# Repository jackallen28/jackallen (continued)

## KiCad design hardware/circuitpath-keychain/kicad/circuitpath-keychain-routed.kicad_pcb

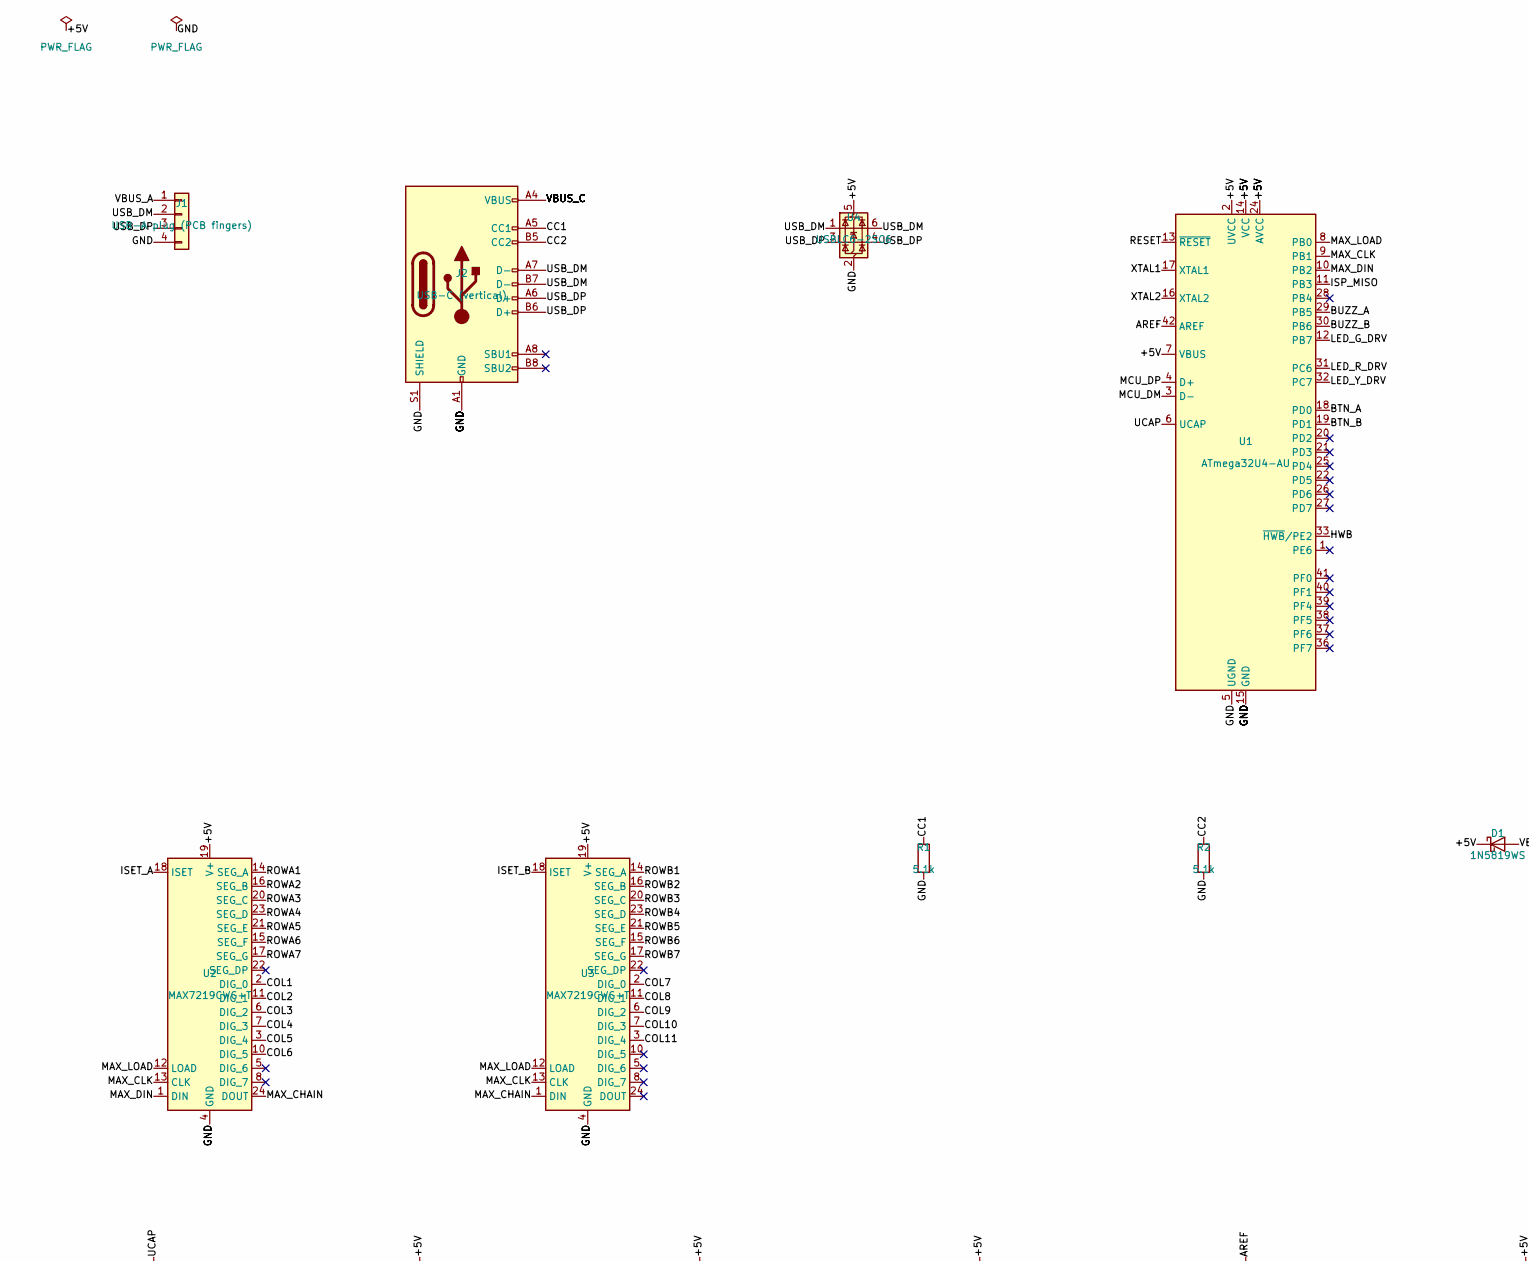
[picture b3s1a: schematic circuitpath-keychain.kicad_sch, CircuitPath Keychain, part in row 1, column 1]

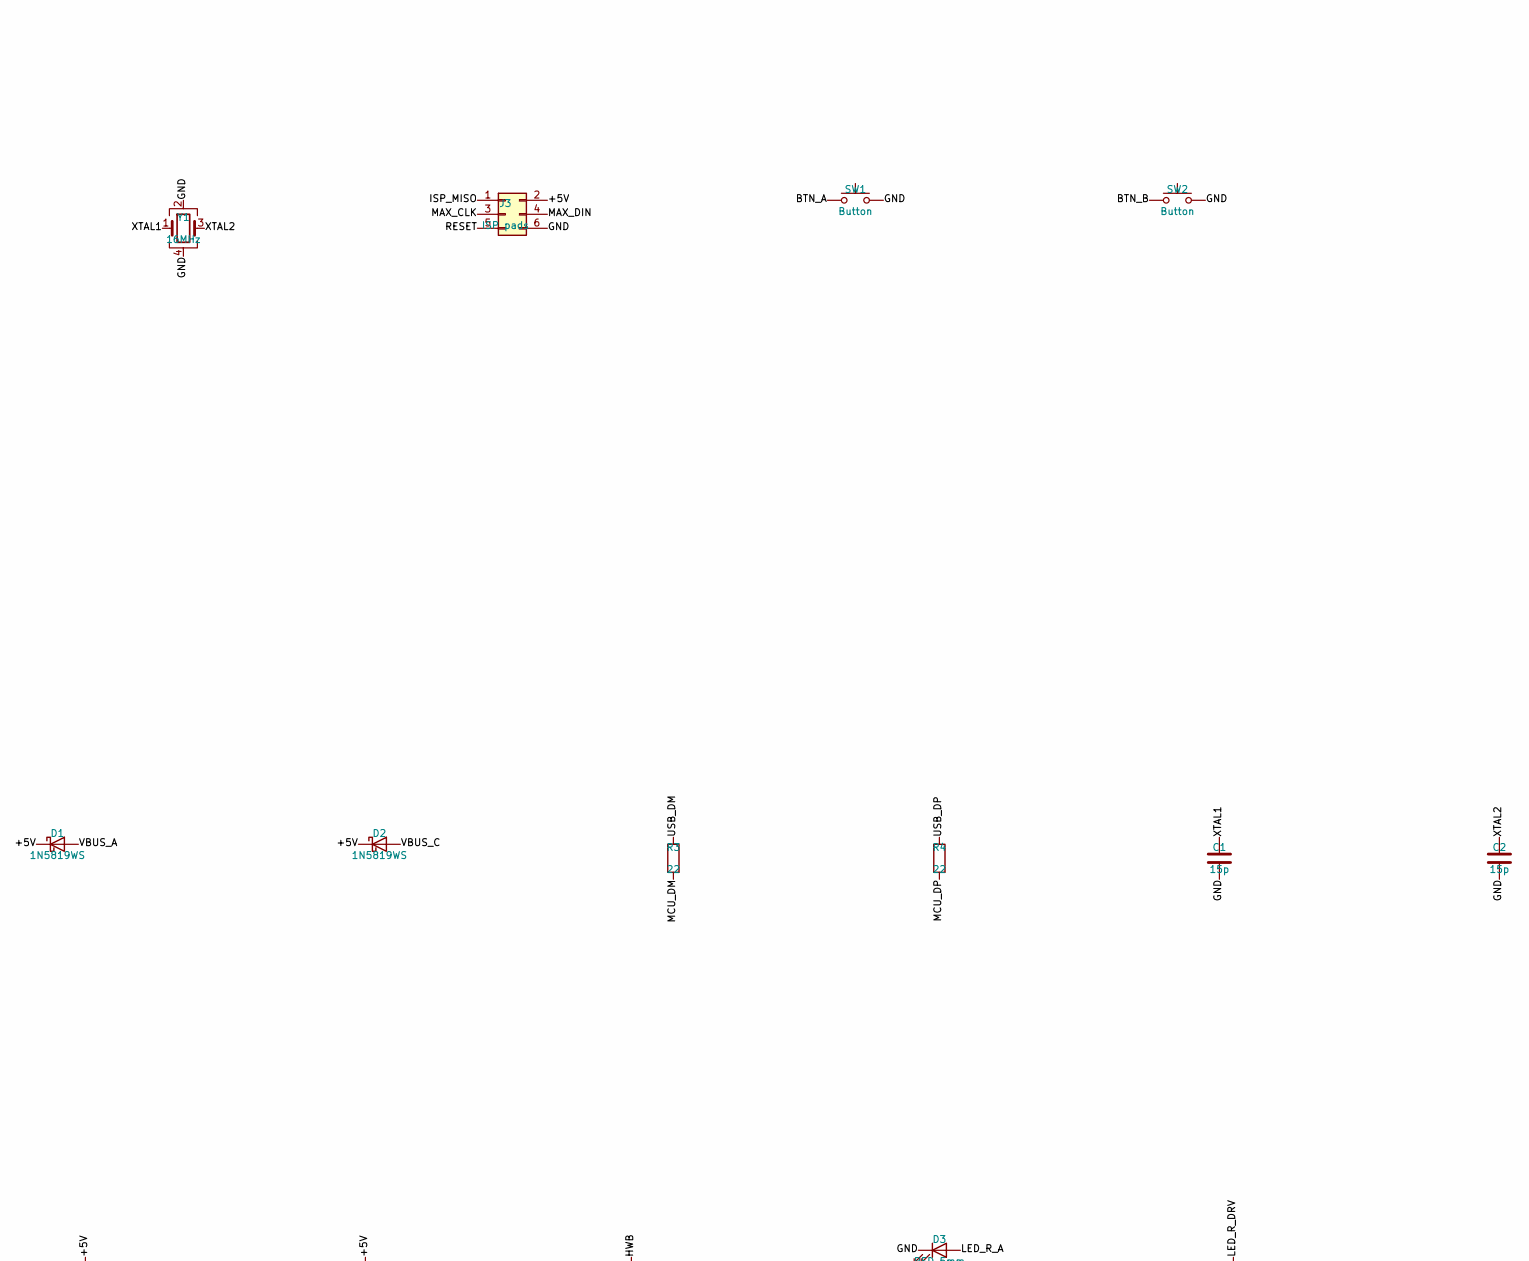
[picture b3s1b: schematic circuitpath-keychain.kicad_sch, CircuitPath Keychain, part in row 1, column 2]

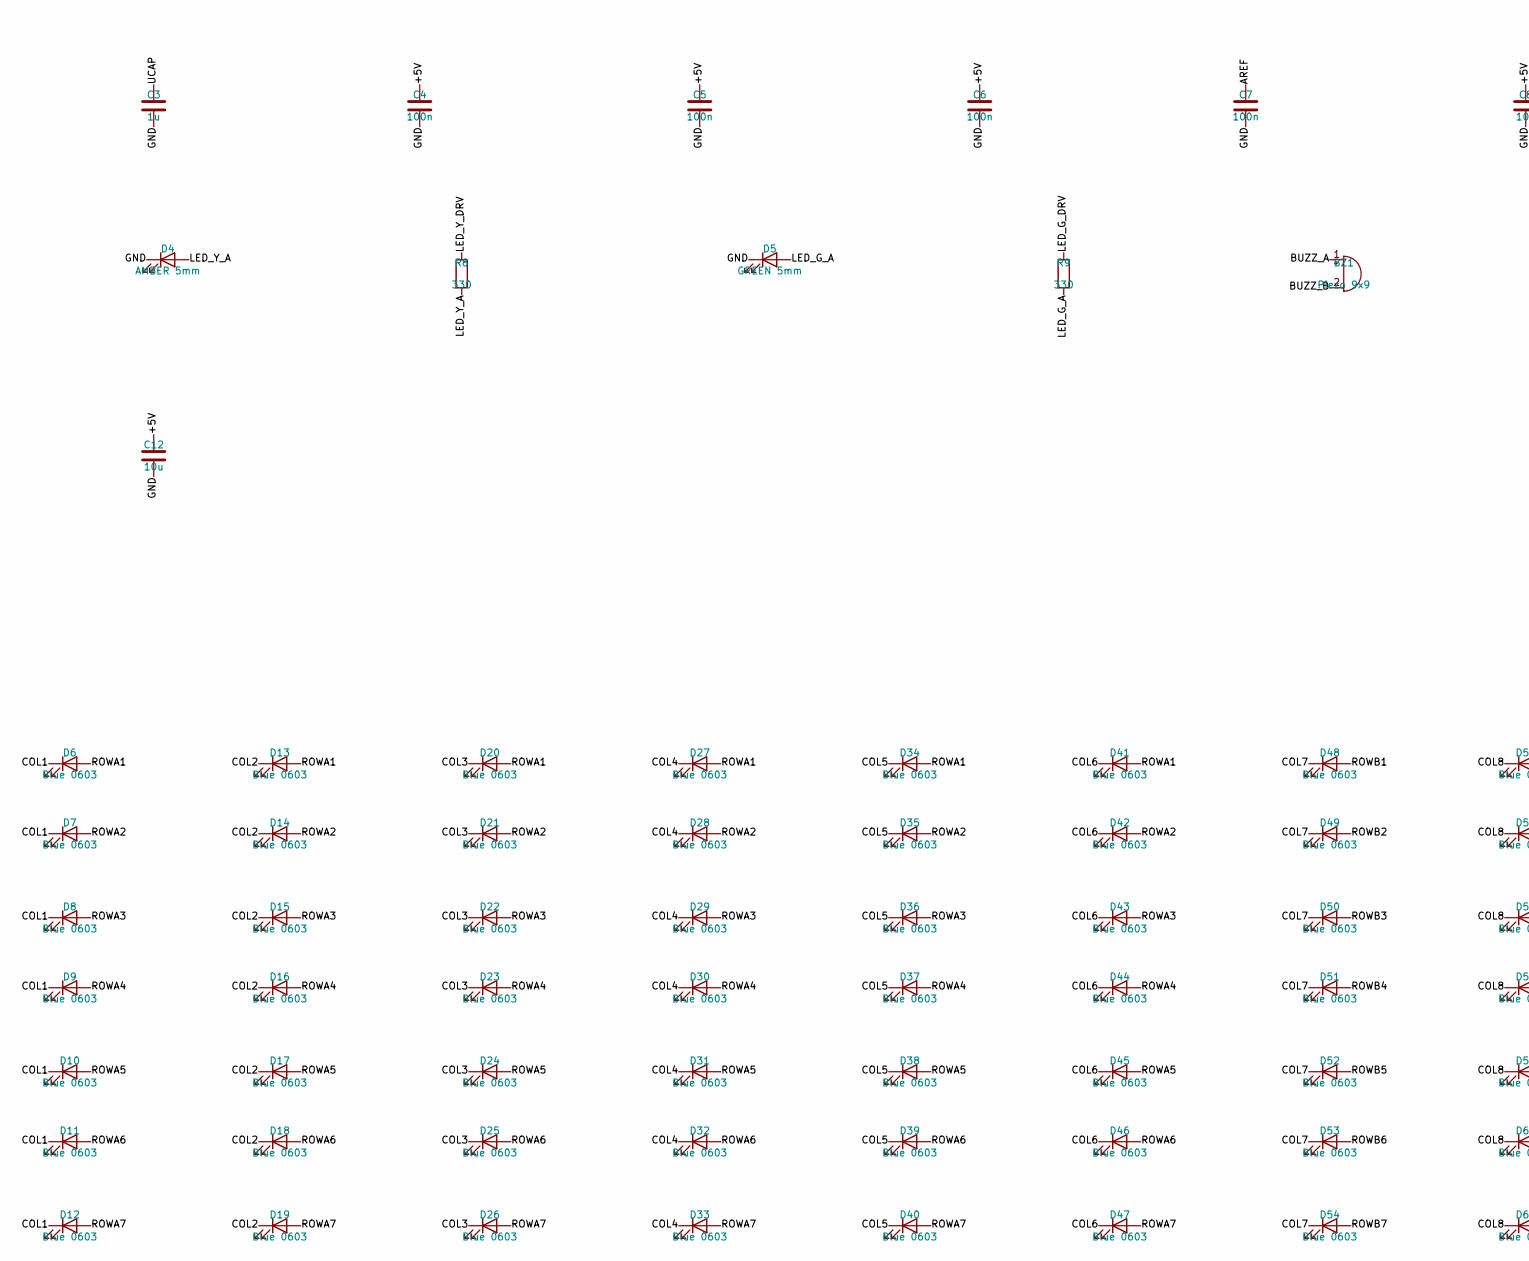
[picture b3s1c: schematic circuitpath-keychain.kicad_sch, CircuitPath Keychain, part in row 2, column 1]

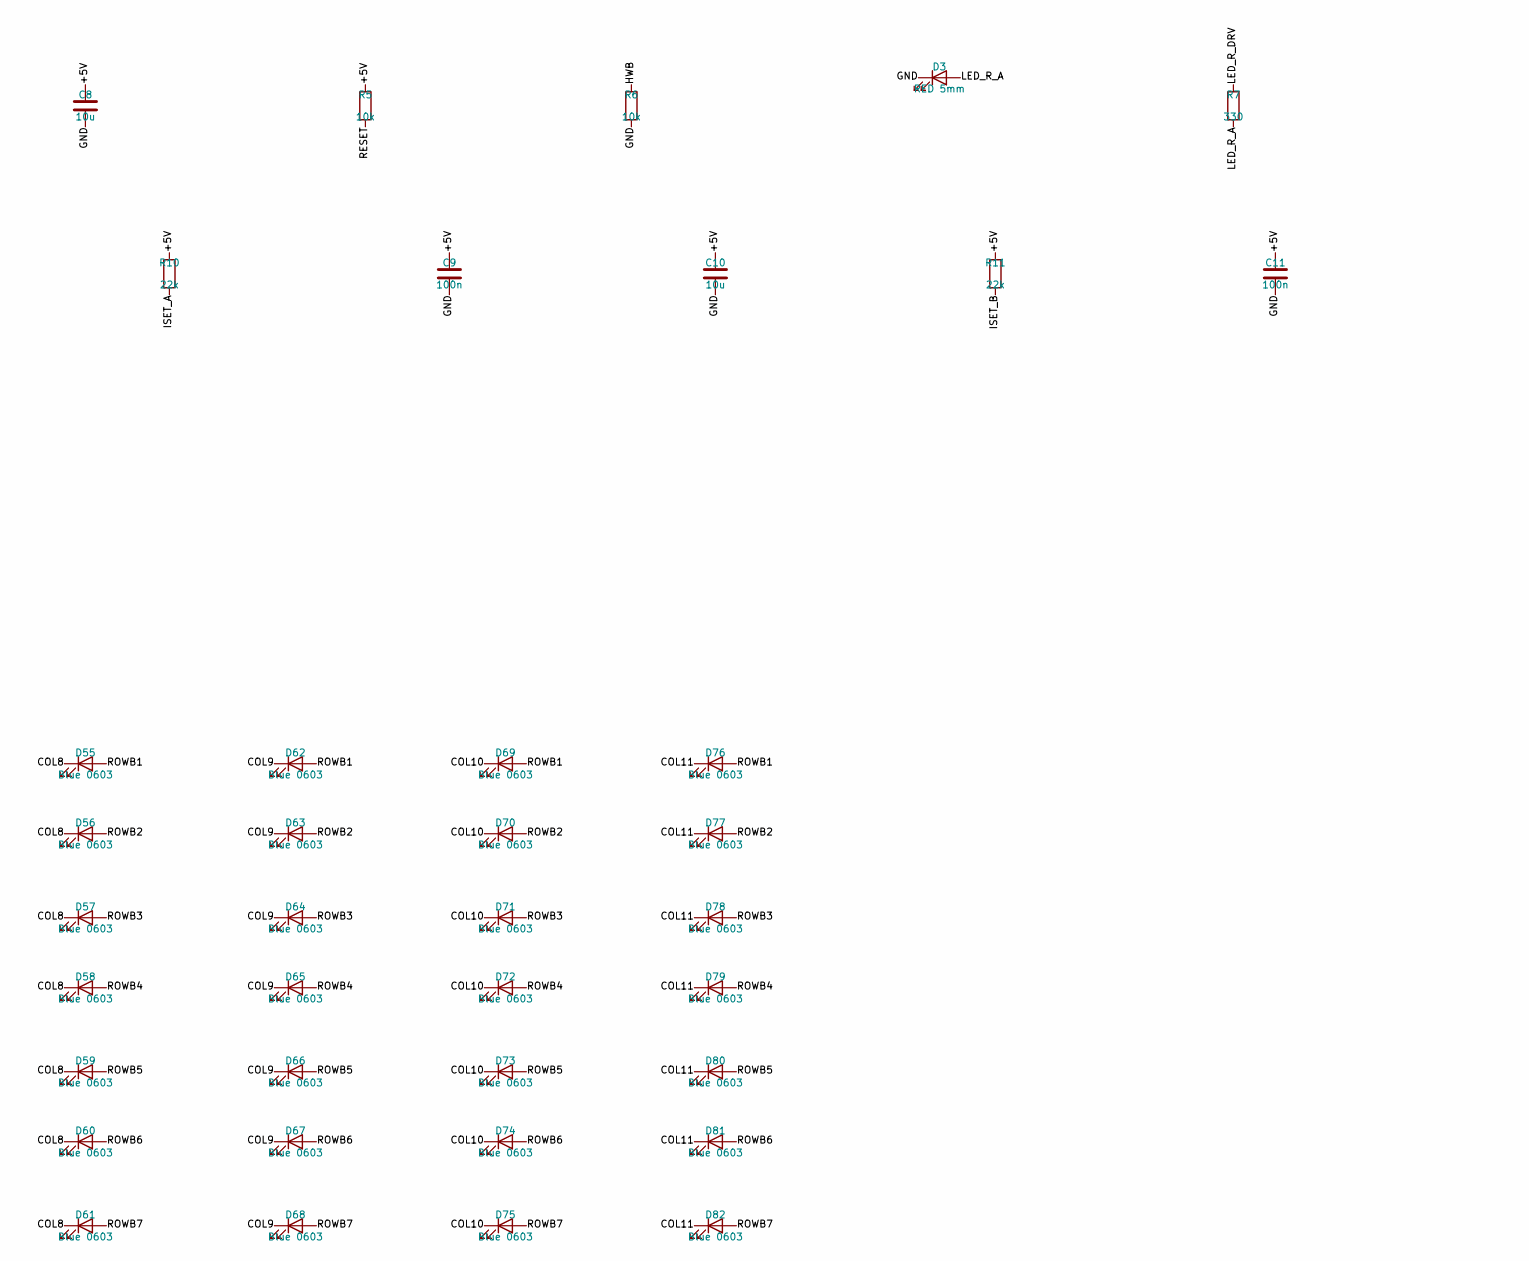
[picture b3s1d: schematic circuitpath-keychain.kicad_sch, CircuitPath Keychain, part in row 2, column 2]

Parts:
BZ1: Piezo 9x9; Buzzer_Murata_PKMCS0909E; MPN PKMCS0909E4000-R1; LCSC C910763
C1, C2: 15p; C_0603_1608Metric; MPN CL10C150JB8NNNC; LCSC C1644
C3: 1u; C_0603_1608Metric; MPN CL10A105KB8NNNC; LCSC C15849
C4, C5, C6, C7, C9, C11: 100n; C_0603_1608Metric; MPN CL10B104KB8NNNC; LCSC C14663
C8, C10, C12: 10u; C_0805_2012Metric; MPN CL21A106KAYNNNE; LCSC C15850
D1, D2: 1N5819WS; D_SOD-323; MPN 1N5819WS; LCSC C191023
D3: RED 5mm; LED_D5.0mm
D4: AMBER 5mm; LED_D5.0mm
D5: GREEN 5mm; LED_D5.0mm
D6, D7, D8, D9, D10, D11, D12, D13, D14, D15, D16, D17, D18, D19, D20, D21, D22, D23, D24, D25, D26, D27, D28, D29, D30, D31, D32, D33, D34, D35, D36, D37, D38, D39, D40, D41, D42, D43, D44, D45, D46, D47, D48, D49, D50, D51, D52, D53, D54, D55, D56, D57, D58, D59, D60, D61, D62, D63, D64, D65, D66, D67, D68, D69, D70, D71, D72, D73, D74, D75, D76, D77, D78, D79, D80, D81, D82: Blue 0603; LED_0603_1608Metric; MPN KT-0603B; LCSC C2288
J1: USB-A plug (PCB fingers); USB_A_PCB_Plug
J2: USB-C (vertical); USB_C_Receptacle_G-Switch_GT-USB-7051x; MPN GT-USB-7051A; LCSC C2843970
J3: ISP pads; ISP_Pads_2x3
R1, R2: 5.1k; R_0603_1608Metric; MPN 0603WAF5101T5E; LCSC C23186
R3, R4: 22; R_0603_1608Metric; MPN 0603WAF220JT5E; LCSC C23345
R5, R6: 10k; R_0603_1608Metric; MPN 0603WAF1002T5E; LCSC C25804
R7, R8, R9: 330; R_0603_1608Metric; MPN 0603WAF3300T5E; LCSC C23138
R10, R11: 22k; R_0603_1608Metric; MPN 0603WAF2202T5E; LCSC C31850
SW1, SW2: Button; SW_Push_1P1T_XKB_TS-1187A; MPN TS-1187A-B-A-B; LCSC C318884
U1: ATmega32U4-AU; TQFP-44_10x10mm_P0.8mm; MPN ATMEGA32U4-AU; LCSC C44854
U2, U3: MAX7219CWG+T; SOIC-24W_7.5x15.4mm_P1.27mm; MPN MAX7219CWG+T; LCSC C9964
U4: USBLC6-2SC6; SOT-23-6; MPN USBLC6-2SC6; LCSC C7519
Y1: 16MHz; Crystal_SMD_3225-4Pin_3.2x2.5mm; MPN X322516MLB4SI; LCSC C13738

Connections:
+5V: C4.1, C5.1, C6.1, C8.1, C9.1, C10.1, C11.1, C12.1, D1.1 (K), D2.1 (K), J3.2, R5.1, R10.1, R11.1, U1.2 (UVCC), U1.7 (VBUS), U1.14 (VCC), U1.24 (AVCC), U1.34 (VCC), U1.44 (AVCC), U2.19 (V+), U3.19 (V+), U4.5 (VBUS)
AREF: C7.1, U1.42 (AREF)
BTN_A: SW1.1, U1.18 (PD0)
BTN_B: SW2.1, U1.19 (PD1)
BUZZ_A: BZ1.1 (+), U1.29 (PB5)
BUZZ_B: BZ1.2 (-), U1.30 (PB6)
CC1: J2.A5 (CC1), R1.1
CC2: J2.B5 (CC2), R2.1
COL1: D6.1 (K), D7.1 (K), D8.1 (K), D9.1 (K), D10.1 (K), D11.1 (K), D12.1 (K), U2.2 (DIG_0)
COL2: D13.1 (K), D14.1 (K), D15.1 (K), D16.1 (K), D17.1 (K), D18.1 (K), D19.1 (K), U2.11 (DIG_1)
COL3: D20.1 (K), D21.1 (K), D22.1 (K), D23.1 (K), D24.1 (K), D25.1 (K), D26.1 (K), U2.6 (DIG_2)
COL4: D27.1 (K), D28.1 (K), D29.1 (K), D30.1 (K), D31.1 (K), D32.1 (K), D33.1 (K), U2.7 (DIG_3)
COL5: D34.1 (K), D35.1 (K), D36.1 (K), D37.1 (K), D38.1 (K), D39.1 (K), D40.1 (K), U2.3 (DIG_4)
COL6: D41.1 (K), D42.1 (K), D43.1 (K), D44.1 (K), D45.1 (K), D46.1 (K), D47.1 (K), U2.10 (DIG_5)
COL7: D48.1 (K), D49.1 (K), D50.1 (K), D51.1 (K), D52.1 (K), D53.1 (K), D54.1 (K), U3.2 (DIG_0)
COL8: D55.1 (K), D56.1 (K), D57.1 (K), D58.1 (K), D59.1 (K), D60.1 (K), D61.1 (K), U3.11 (DIG_1)
COL9: D62.1 (K), D63.1 (K), D64.1 (K), D65.1 (K), D66.1 (K), D67.1 (K), D68.1 (K), U3.6 (DIG_2)
COL10: D69.1 (K), D70.1 (K), D71.1 (K), D72.1 (K), D73.1 (K), D74.1 (K), D75.1 (K), U3.7 (DIG_3)
COL11: D76.1 (K), D77.1 (K), D78.1 (K), D79.1 (K), D80.1 (K), D81.1 (K), D82.1 (K), U3.3 (DIG_4)
GND: C1.2, C2.2, C3.2, C4.2, C5.2, C6.2, C7.2, C8.2, C9.2, C10.2, C11.2, C12.2, D3.1 (K), D4.1 (K), D5.1 (K), J1.4, J2.A1 (GND), J2.A12 (GND), J2.B1 (GND), J2.B12 (GND), J2.S1 (SHIELD), J3.6, R1.2, R2.2, R6.2, SW1.2, SW2.2, U1.5 (UGND), U1.15 (GND), U1.23 (GND), U1.35 (GND), U1.43 (GND), U2.4 (GND), U2.9 (GND), U3.4 (GND), U3.9 (GND), U4.2 (GND), Y1.2, Y1.4
HWB: R6.1, U1.33 (~HWB/PE2)
ISET_A: R10.2, U2.18 (ISET)
ISET_B: R11.2, U3.18 (ISET)
ISP_MISO: J3.1, U1.11 (PB3)
LED_G_A: D5.2 (A), R9.2
LED_G_DRV: R9.1, U1.12 (PB7)
LED_R_A: D3.2 (A), R7.2
LED_R_DRV: R7.1, U1.31 (PC6)
LED_Y_A: D4.2 (A), R8.2
LED_Y_DRV: R8.1, U1.32 (PC7)
MAX_CHAIN: U2.24 (DOUT), U3.1 (DIN)
MAX_CLK: J3.3, U1.9 (PB1), U2.13 (CLK), U3.13 (CLK)
MAX_DIN: J3.4, U1.10 (PB2), U2.1 (DIN)
MAX_LOAD: U1.8 (PB0), U2.12 (LOAD), U3.12 (LOAD)
MCU_DM: R3.2, U1.3 (D-)
MCU_DP: R4.2, U1.4 (D+)
RESET: J3.5, R5.2, U1.13 (~RESET)
ROWA1: D6.2 (A), D13.2 (A), D20.2 (A), D27.2 (A), D34.2 (A), D41.2 (A), U2.14 (SEG_A)
ROWA2: D7.2 (A), D14.2 (A), D21.2 (A), D28.2 (A), D35.2 (A), D42.2 (A), U2.16 (SEG_B)
ROWA3: D8.2 (A), D15.2 (A), D22.2 (A), D29.2 (A), D36.2 (A), D43.2 (A), U2.20 (SEG_C)
ROWA4: D9.2 (A), D16.2 (A), D23.2 (A), D30.2 (A), D37.2 (A), D44.2 (A), U2.23 (SEG_D)
ROWA5: D10.2 (A), D17.2 (A), D24.2 (A), D31.2 (A), D38.2 (A), D45.2 (A), U2.21 (SEG_E)
ROWA6: D11.2 (A), D18.2 (A), D25.2 (A), D32.2 (A), D39.2 (A), D46.2 (A), U2.15 (SEG_F)
ROWA7: D12.2 (A), D19.2 (A), D26.2 (A), D33.2 (A), D40.2 (A), D47.2 (A), U2.17 (SEG_G)
ROWB1: D48.2 (A), D55.2 (A), D62.2 (A), D69.2 (A), D76.2 (A), U3.14 (SEG_A)
ROWB2: D49.2 (A), D56.2 (A), D63.2 (A), D70.2 (A), D77.2 (A), U3.16 (SEG_B)
ROWB3: D50.2 (A), D57.2 (A), D64.2 (A), D71.2 (A), D78.2 (A), U3.20 (SEG_C)
ROWB4: D51.2 (A), D58.2 (A), D65.2 (A), D72.2 (A), D79.2 (A), U3.23 (SEG_D)
ROWB5: D52.2 (A), D59.2 (A), D66.2 (A), D73.2 (A), D80.2 (A), U3.21 (SEG_E)
ROWB6: D53.2 (A), D60.2 (A), D67.2 (A), D74.2 (A), D81.2 (A), U3.15 (SEG_F)
ROWB7: D54.2 (A), D61.2 (A), D68.2 (A), D75.2 (A), D82.2 (A), U3.17 (SEG_G)
UCAP: C3.1, U1.6 (UCAP)
USB_DM: J1.2, J2.A7 (D-), J2.B7 (D-), R3.1, U4.1 (I/O1), U4.6 (I/O1)
USB_DP: J1.3, J2.A6 (D+), J2.B6 (D+), R4.1, U4.3 (I/O2), U4.4 (I/O2)
VBUS_A: D1.2 (A), J1.1
VBUS_C: D2.2 (A), J2.A4 (VBUS), J2.A9 (VBUS), J2.B4 (VBUS), J2.B9 (VBUS)
XTAL1: C1.1, U1.17 (XTAL1), Y1.1
XTAL2: C2.1, U1.16 (XTAL2), Y1.3

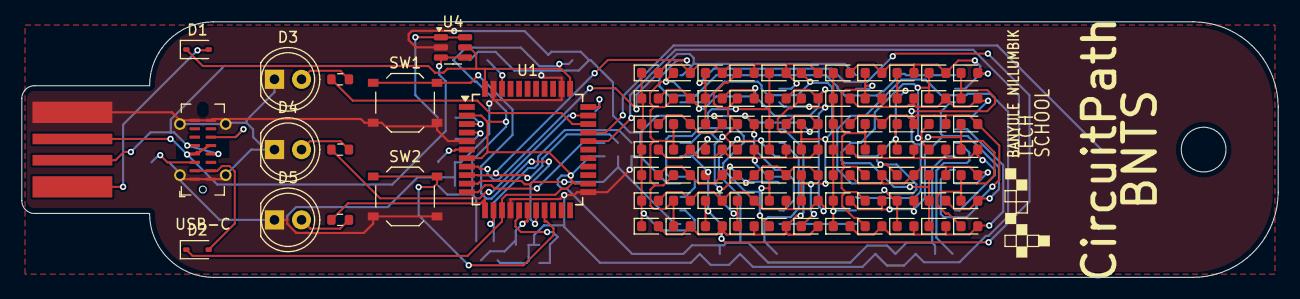
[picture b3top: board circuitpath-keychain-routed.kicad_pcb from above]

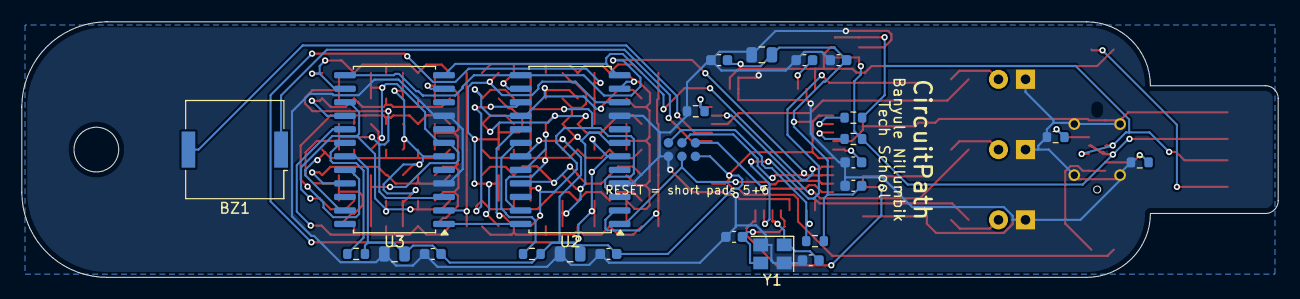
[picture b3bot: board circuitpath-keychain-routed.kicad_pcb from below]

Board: 2 copper layers, 118.0 x 24.0 mm, 116 parts (25 on the bottom side), 58 nets.

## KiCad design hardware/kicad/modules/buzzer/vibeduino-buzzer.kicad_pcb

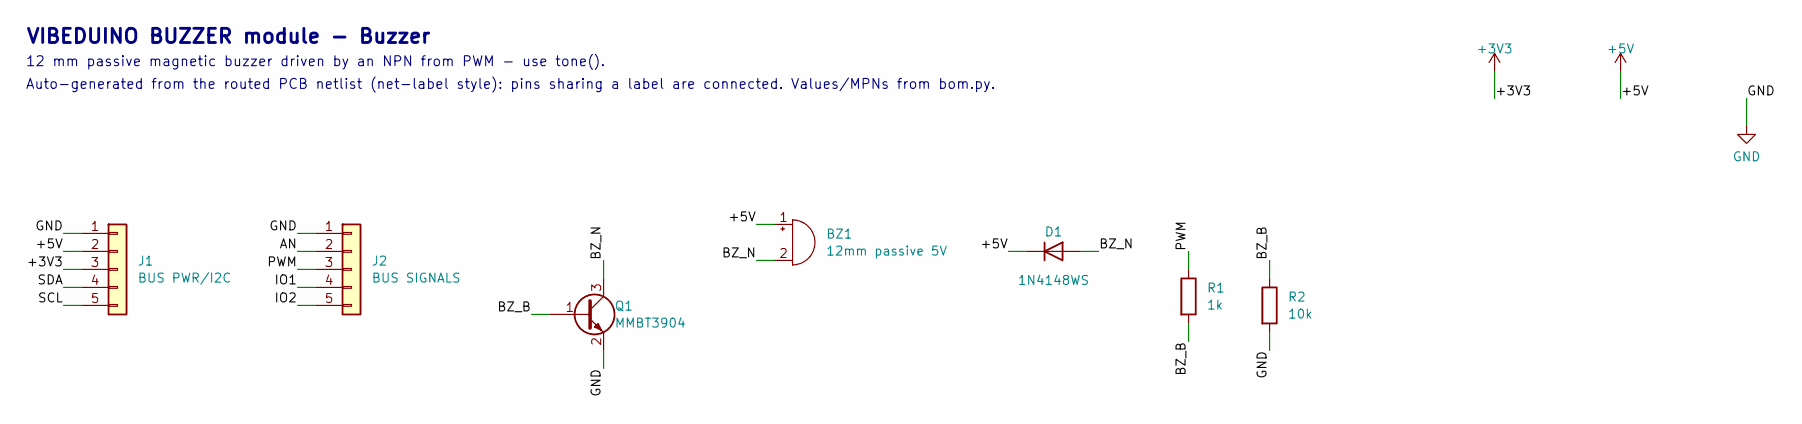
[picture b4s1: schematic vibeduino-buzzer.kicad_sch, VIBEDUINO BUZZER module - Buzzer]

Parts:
BZ1: 12mm passive 5V; Buzzer_12x9.5RM7.6; MPN — (passive, no oscillator)
D1: 1N4148WS; D_SOD-323; MPN 1N4148WS; LCSC C2128
J1: BUS PWR/I2C; PinHeader_1x05_P2.54mm_Vertical; MPN PZ254V-11-05P; LCSC C492404
J2: BUS SIGNALS; PinHeader_1x05_P2.54mm_Vertical; MPN PZ254V-11-05P; LCSC C492404
Q1: MMBT3904; SOT-23; MPN MMBT3904; LCSC C20526
R1: 1k; R_0603_1608Metric; MPN 0603WAF1001T5E; LCSC C21190
R2: 10k; R_0603_1608Metric; MPN 0603WAF1002T5E; LCSC C25804

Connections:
+3V3: J1.3
+5V: BZ1.1 (+), D1.1 (K), J1.2
AN: J2.2
BZ_B: Q1.1 (B), R1.2, R2.1
BZ_N: BZ1.2 (-), D1.2 (A), Q1.3 (C)
GND: J1.1, J2.1, Q1.2 (E), R2.2
IO1: J2.4
IO2: J2.5
PWM: J2.3, R1.1
SCL: J1.5
SDA: J1.4

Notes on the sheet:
VIBEDUINO BUZZER module - Buzzer
12 mm passive magnetic buzzer driven by an NPN from PWM - use tone().
Auto-generated from the routed PCB netlist (net-label style): pins sharing a label are connected. Values/MPNs from bom.py.

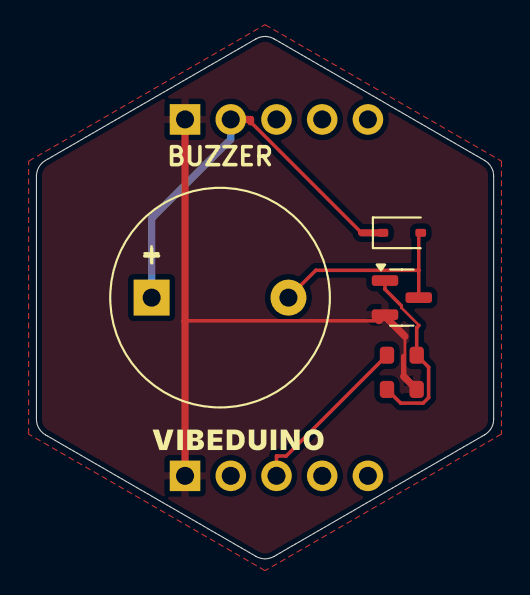
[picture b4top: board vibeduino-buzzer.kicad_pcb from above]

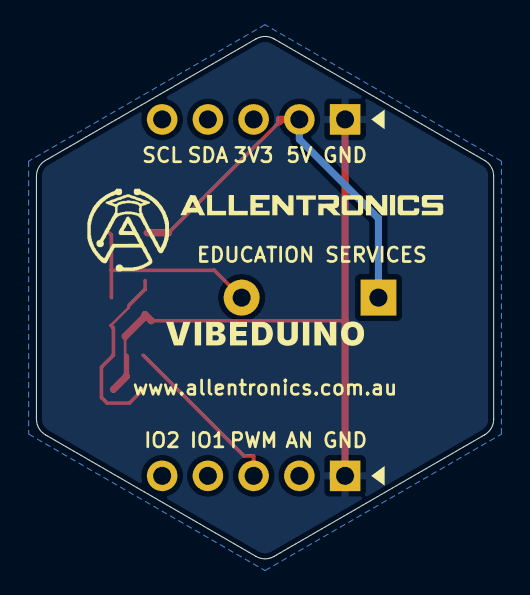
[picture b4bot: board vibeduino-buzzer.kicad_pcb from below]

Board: 2 copper layers, 25.4 x 29.0 mm, 7 parts (2 on the bottom side), 5 nets.

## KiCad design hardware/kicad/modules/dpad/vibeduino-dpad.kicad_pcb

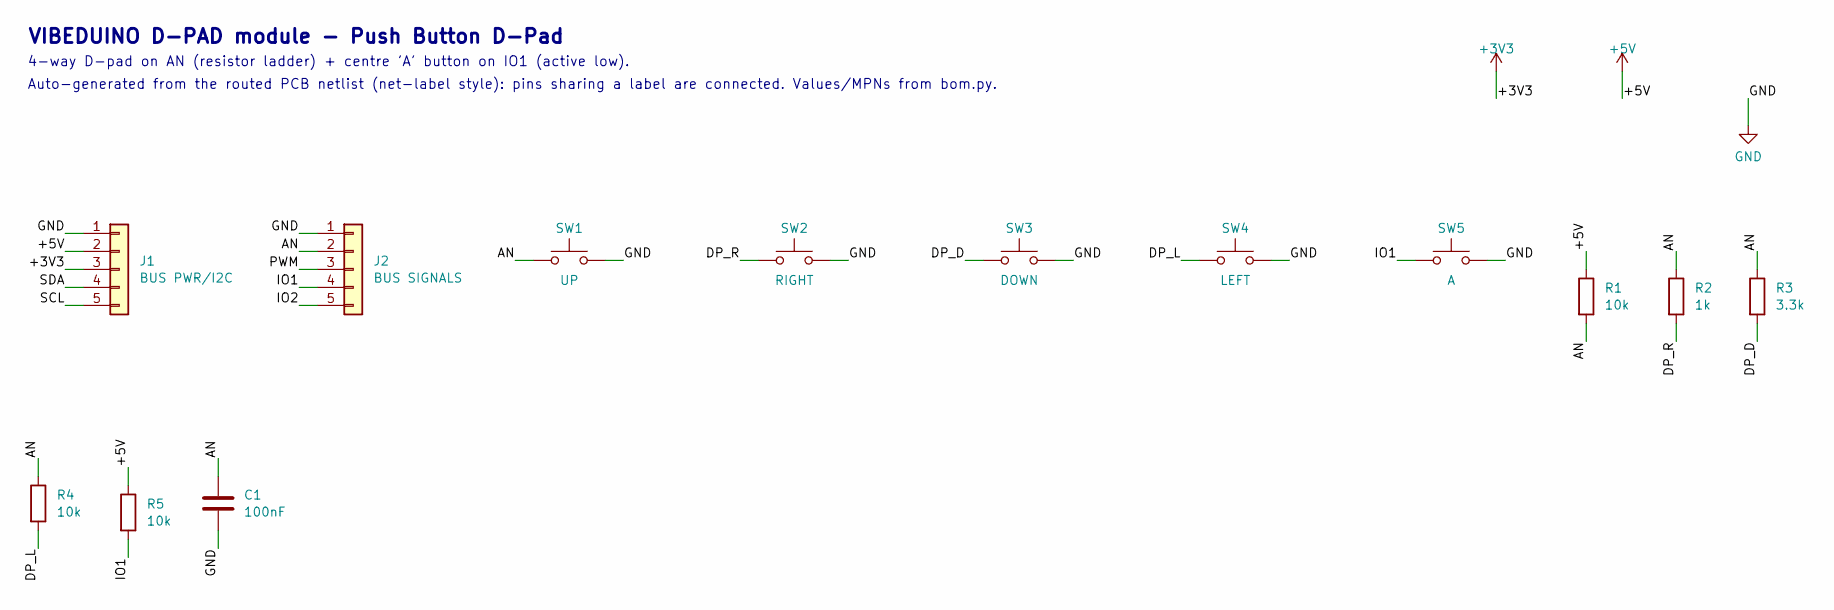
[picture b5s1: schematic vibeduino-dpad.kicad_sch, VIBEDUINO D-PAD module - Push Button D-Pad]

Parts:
C1: 100nF; C_0603_1608Metric; MPN CC0603KRX7R9BB104; LCSC C14663
J1: BUS PWR/I2C; PinHeader_1x05_P2.54mm_Vertical; MPN PZ254V-11-05P; LCSC C492404
J2: BUS SIGNALS; PinHeader_1x05_P2.54mm_Vertical; MPN PZ254V-11-05P; LCSC C492404
R1, R4, R5: 10k; R_0603_1608Metric; MPN 0603WAF1002T5E; LCSC C25804
R2: 1k; R_0603_1608Metric; MPN 0603WAF1001T5E; LCSC C21190
R3: 3.3k; R_0603_1608Metric; MPN 0603WAF3301T5E; LCSC C22978
SW1: UP; SW_Push_1P1T_XKB_TS-1187A; MPN TS-1187A-B-A-B; LCSC C318884
SW2: RIGHT; SW_Push_1P1T_XKB_TS-1187A; MPN TS-1187A-B-A-B; LCSC C318884
SW3: DOWN; SW_Push_1P1T_XKB_TS-1187A; MPN TS-1187A-B-A-B; LCSC C318884
SW4: LEFT; SW_Push_1P1T_XKB_TS-1187A; MPN TS-1187A-B-A-B; LCSC C318884
SW5: A; SW_Push_1P1T_XKB_TS-1187A; MPN TS-1187A-B-A-B; LCSC C318884

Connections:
+3V3: J1.3
+5V: J1.2, R1.1, R5.1
AN: C1.1, J2.2, R1.2, R2.1, R3.1, R4.1, SW1.1
DP_D: R3.2, SW3.1
DP_L: R4.2, SW4.1
DP_R: R2.2, SW2.1
GND: C1.2, J1.1, J2.1, SW1.2, SW2.2, SW3.2, SW4.2, SW5.2
IO1: J2.4, R5.2, SW5.1
IO2: J2.5
PWM: J2.3
SCL: J1.5
SDA: J1.4

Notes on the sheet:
VIBEDUINO D-PAD module - Push Button D-Pad
4-way D-pad on AN (resistor ladder) + centre 'A' button on IO1 (active low).
Auto-generated from the routed PCB netlist (net-label style): pins sharing a label are connected. Values/MPNs from bom.py.

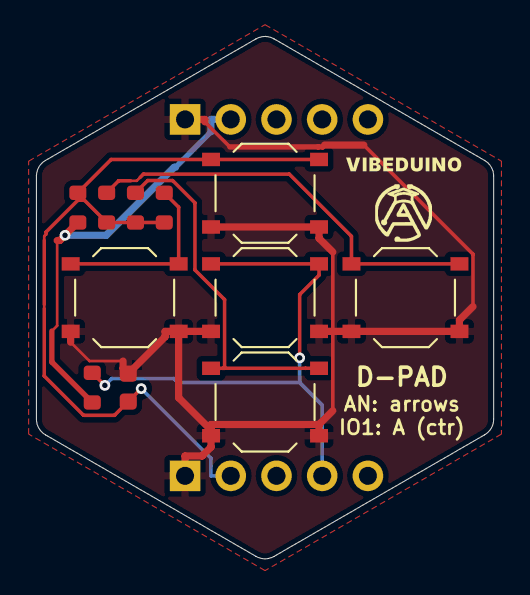
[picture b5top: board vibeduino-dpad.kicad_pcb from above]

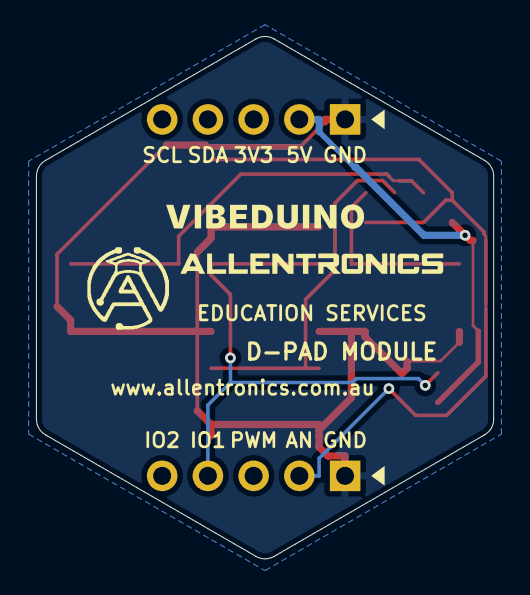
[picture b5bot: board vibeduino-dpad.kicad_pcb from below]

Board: 2 copper layers, 25.4 x 29.0 mm, 13 parts (2 on the bottom side), 7 nets.
